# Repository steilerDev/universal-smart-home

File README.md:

# universal-smart-home

ESPHome firmware for the house: ~25 room sensor units plus a handful of special-purpose
nodes. Every device is an [Olimex ESP32-POE2](https://www.olimex.com/Products/IoT/ESP32/ESP32-POE2/open-source-hardware)
on PoE Ethernet — no WiFi, no cloud dependency. All devices integrate with Home
Assistant via the native ESPHome API. This repo is the single source of truth for
every device configuration.

---

## Hardware — Room Sensor

> [Schematic](https://app.cirkitdesigner.com/project/281a6c22-06b7-4593-8d16-d8be4f0f2b7c)

| Component | Part |
|-----------|------|
| MCU | [Olimex ESP32-POE2](https://www.olimex.com/Products/IoT/ESP32/ESP32-POE2/open-source-hardware) (ESP32-WROVER-E, PoE Ethernet) |
| Climate | [ENS160](https://esphome.io/components/sensor/ens160/) + [AHT21](https://esphome.io/components/sensor/aht10/) — eCO2, TVOC, AQI, temp, humidity |
| Illuminance | [BH1750](https://esphome.io/components/sensor/bh1750/) |
| Presence | [DFRobot C4002](https://www.dfrobot.com/product-3081.html) mmWave radar (custom component) |
| Dimmer | [KRIDA I2C AC dimmer](https://www.tindie.com/products/bugrovs2012/i2c-mosfet-trailing-edge-ac-dimmer-light) trailing-edge MOSFET (custom component) |
| GPIO Expander | [PCF8574](https://esphome.io/components/pcf8574/) — 2 buttons, 2 power circuits, 2 roller blinds |
| Status LED | WS2811/WS2812 via [esp32_rmt_led_strip](https://esphome.io/components/light/esp32_rmt_led_strip/) |
| Audio | [ES8311](https://esphome.io/components/audio_dac/es8311/) + NS4150B (notifications / TTS) |
| Power | [PZEM-004T](https://esphome.io/components/sensor/pzemac/) AC energy monitor |

PCB design files live in `hardware/pcb/`, the enclosure in `hardware/case/room-sensor/`.

---

## Hardware — Utility Sensor

The basement metering node. Same Olimex board, **no custom PCB** — the field wiring
lands on screw terminals — but it does have its own case (`hardware/case/utility-sensor/`).

| Component | Part |
|-----------|------|
| MCU | Olimex ESP32-POE2, running the `esp-idf` framework (8 × PCNT pulse counters) |
| Water flow | 8 × YF-B series hall-effect meters, one per supply line |
| Well level | QDY30A submersible level transmitter (Modbus RTU over RS485) |
| Grid power | Eastron SDM three-phase meter (Modbus RTU) — wired for, **not yet populated** |

Schematic (WIP): https://app.cirkitdesigner.com/project/46fdfdfb-f6f8-4aec-ac91-cfc2bc7dc07d

### Metered lines

| Line | GPIO | Line | GPIO |
|------|------|------|------|
| EG Kalt | GPIO04 | EG Warm | GPIO36 |
| OG Kalt | GPIO33 | OG Warm | GPIO13 |
| EG Heizung | GPIO15 | OG Heizung | GPIO02 |
| Anbau Heizung | GPIO14 | Brunnen | GPIO05 |

### Calibration

Both are build-time values in `devices/utility-sensor.yaml` — change and re-flash.

- **Water meters** — `flow_pulses_per_liter` per line. Meter datasheets quote
  `F = K * Q` (F in Hz, Q in L/min), so pulses/L is `K * 60`; the YF-B's K = 6.6 gives
  396. Each line carries its own value, so lines with a different meter model just get
  a different number.

  After changing a line's calibration, **re-flash and then press its
  `Water Volume Reset - <line>` button in HA**. The running total is stored in flash
  keyed by entity, so it survives the OTA and would otherwise keep the volume that
  was accumulated with the old pulses/L.
- **Well level** — the probe measures the water column above *itself*. The published
  value is the column above the **pump intake**:
  `raw + (well_pump_depth_cm - well_sensor_depth_cm)`. The offset is +100 cm in this
  install (probe at 15 m, intake at 16 m); it would be negative if the probe hung
  below the intake. Negative readings mean the water is below the intake and are not
  clamped away.

  ⚠️ Because the probe sits **above** the intake it cannot see a surface below itself,
  so the last 100 cm above the intake all read 100 cm — a floor, not a level. The
  `Well Probe Uncovered` binary sensor (`device_class: problem`) is ON exactly then, so
  automations can treat that reading as "≤100 cm, unknown" rather than trusting it.
  Hanging the probe below the intake would remove the blind spot.

### Home Assistant water dashboard

The `Water Volume - <line>` sensors carry `device_class: water` +
`state_class: total_increasing`, which is what HA's water dashboard filters on. A unit
of `L` alone is not enough — the entity simply never appears in the picker without
both of those.

---

## Repository Layout

```
devices/          — One YAML per physical device (substitutions + package includes)
packages/
  base/           — Board, Ethernet, OTA, HA API (room-sensor / utility-sensor variants)
  sensors/        — climate, illuminance, motion, power-pzem004t, water-flow,
                    well-level, energy-sdm
  actuators/      — status-led, dimmer, audio
  io/             — gpio-extender (PCF8574 — buttons, power circuits, blinds)
  displays/       — trmnl (e-ink dashboard)
components/       — Local custom ESPHome components (dfrobot_c4002, krida_dimmer, trmnl)
hardware/
  pcb/            — KiCad projects, symbol/footprint libs, LCSC BOM
  case/           — Fusion 360 enclosures, one directory per device
deploy/           — Device Builder deployment notes
scripts/          — validate-all, builder-deploy, deploy, new-device, check-device
sounds/           — WAV assets for the audio package
secrets.template.yaml
```

---

## Deployed Devices

| Device | IP | Packages |
|--------|----|---------|
| `room-sensor-poe2` (prototype) | 10.10.14.20 | base, power, climate, motion, status\_led |
| `eink-dashboard` | 10.10.14.25 | base, trmnl |
| `utility-sensor` | 10.10.14.10 | base, well\_level, 8 × water\_flow |

---

## Quick Start

Firmware is compiled and OTA-flashed by the self-hosted **ESPHome Device Builder**,
not by compiling locally — see [`deploy/README.md`](deploy/README.md).

```bash
cp secrets.template.yaml secrets.yaml  # fill in OTA password + HA encryption key

esphome config devices/<name>.yaml     # 1. validate (cheap, no compile)
./scripts/builder-deploy.py <name>     # 2. compile + OTA on the builder
./scripts/check-device.py <name>       # 3. post-deploy health check
```

Add a new device:

```bash
./scripts/new-device.sh <room-name>
```

Local compilation (`pip3 install esphome --break-system-packages`, then
`esphome run devices/<name>.yaml`) still works as a fallback; see `CLAUDE.md` for the
PlatformIO workarounds it needs.

---

## Packages

Each device YAML picks only the packages it needs. Every device requires exactly one
`base` package; the rest are optional.

| Package | Provides |
|---------|----------|
| `base/room-sensor` | Board (arduino), Ethernet PoE, OTA, HA API, I2C bus |
| `base/utility-sensor` | Board (esp-idf), Ethernet PoE, OTA, HA API — no I2C |
| `sensors/climate` | [ENS160](https://esphome.io/components/sensor/ens160/) + [AHT20](https://esphome.io/components/sensor/aht10/) — air quality, temp, humidity |
| `sensors/illuminance` | [BH1750](https://esphome.io/components/sensor/bh1750/) light level |
| `sensors/motion` | [DFRobot C4002](https://www.dfrobot.com/product-3081.html) presence + target tracking |
| `sensors/power-pzem004t` | [PZEM-004T](https://esphome.io/components/sensor/pzemac/) AC voltage/current/power/energy |
| `sensors/water-flow` | Pulse water meter for one supply line — include once per line with `vars` |
| `sensors/well-level` | QDY30A submersible level transmitter over Modbus |
| `sensors/energy-sdm` | Eastron SDM three-phase grid meter over Modbus |
| `actuators/dimmer` | [KRIDA I2C AC dimmer](https://www.tindie.com/products/bugrovs2012/i2c-mosfet-trailing-edge-ac-dimmer-light) (light entity) |
| `actuators/status-led` | WS2811/WS2812 status LED via [esp32_rmt_led_strip](https://esphome.io/components/light/esp32_rmt_led_strip/) |
| `actuators/audio` | [ES8311](https://esphome.io/components/audio_dac/es8311/) I2S media player |
| `io/gpio-extender` | [PCF8574](https://esphome.io/components/pcf8574/) — buttons, switches, blind covers |
| `displays/trmnl` | TRMNL BYOS e-ink dashboard client (custom component) |

`sensors/water-flow` is the one package meant to be included several times per device.
Use the mapping form of `!include` to pass it per-instance variables:

```yaml
packages:
  flow_eg_kalt: !include
    file: ../packages/sensors/water-flow.yaml
    vars:
      flow_key: eg_kalt
      flow_name: "EG Kalt"
      flow_pin: "GPIO04"
      flow_pulses_per_liter: "396"
```

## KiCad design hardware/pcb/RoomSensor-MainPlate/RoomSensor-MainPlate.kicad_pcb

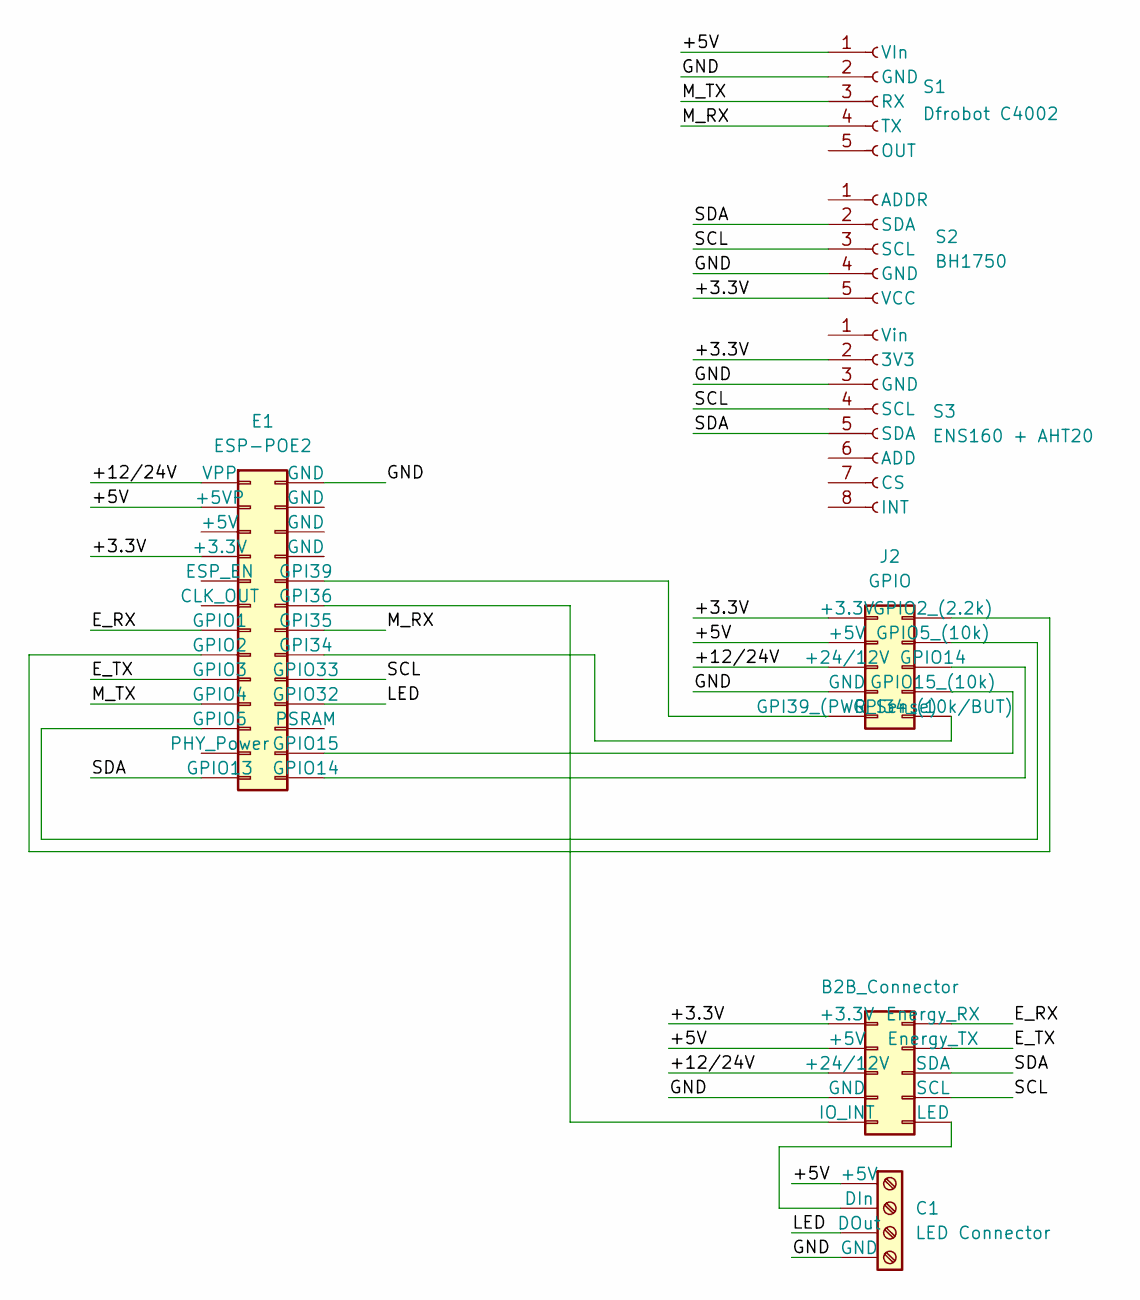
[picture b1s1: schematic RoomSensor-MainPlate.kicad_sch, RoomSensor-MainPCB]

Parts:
C1: LED Connector; TerminalBlock_Phoenix_MPT-0,5-4-2.54_1x04_P2.54mm_Horizontal; MPN KF128-2.54-4P
E1: ESP-POE2; PinSocket_2x13_P2.54mm_Vertical; MPN C64320
J1: B2B_Connector; B2B Connector; MPN MTB10-10S
J2: GPIO; IDC-Header_2x05_P2.54mm_Vertical; MPN MTB10-10S
S1: Dfrobot C4002; DFRobot C4002 Connector; MPN C50950
S2: BH1750; MPN C50950
S3: ENS160 + AHT20; ENS160 + AHT20 Connector; MPN C27438

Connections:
/+3.3V: E1.7 (+3.3V), J1.1 (+3.3V), J2.1 (+3.3V), S2.5 (VCC), S3.2 (3V3)
/+5V: C1.1 (+5V), E1.3 (+5VP), J1.3 (+5V), J2.3 (+5V), S1.1 (VIn)
/+12/24V: E1.1 (VPP), J1.5 (+24/12V), J2.5 (+24/12V)
/E_RX: E1.13 (GPIO1), J1.2 (Energy_RX)
/E_TX: E1.17 (GPIO3), J1.4 (Energy_TX)
/GND: C1.4 (GND), E1.2 (GND), J1.7 (GND), J2.7 (GND), S1.2 (GND), S2.4 (GND), S3.3 (GND)
/LED: C1.3 (DOut), E1.20 (GPIO32)
/M_RX: E1.14 (GPI35), S1.4 (TX)
/M_TX: E1.19 (GPIO4), S1.3 (RX)
/SCL: E1.18 (GPIO33), J1.8 (SCL), S2.3 (SCL), S3.4 (SCL)
/SDA: E1.25 (GPIO13), J1.6 (SDA), S2.2 (SDA), S3.5 (SDA)
unnamed: C1.2 (DIn), J1.10 (LED)
unnamed: E1.16 (GPI34), J2.10 (GPI34_(10k/BUT))
unnamed: E1.12 (GPI36), J1.9 (IO_INT)
unnamed: E1.10 (GPI39), J2.9 (GPI39_(PWR_Sense))
unnamed: E1.15 (GPIO2), J2.2 (GPIO2_(2.2k))
unnamed: E1.21 (GPIO5), J2.4 (GPIO5_(10k))
unnamed: E1.26 (GPIO14), J2.6 (GPIO14)
unnamed: E1.24 (GPIO15), J2.8 (GPIO15_(10k))

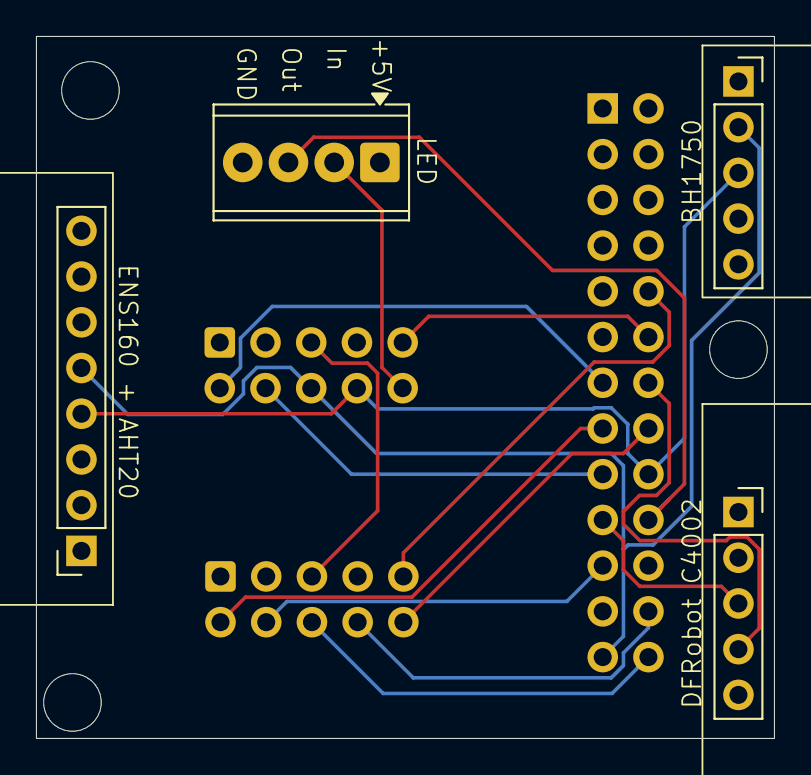
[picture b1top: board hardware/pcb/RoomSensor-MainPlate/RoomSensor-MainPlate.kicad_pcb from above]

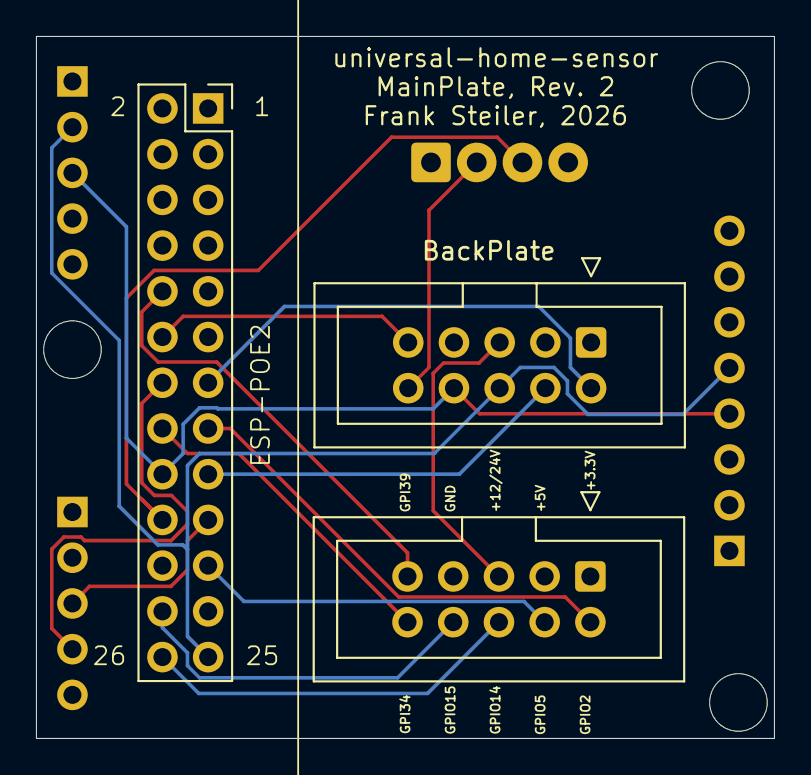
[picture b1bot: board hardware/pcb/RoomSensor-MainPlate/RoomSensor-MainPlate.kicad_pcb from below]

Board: 4 copper layers, 41.0 x 39.0 mm, 7 parts (3 on the bottom side), 19 nets.

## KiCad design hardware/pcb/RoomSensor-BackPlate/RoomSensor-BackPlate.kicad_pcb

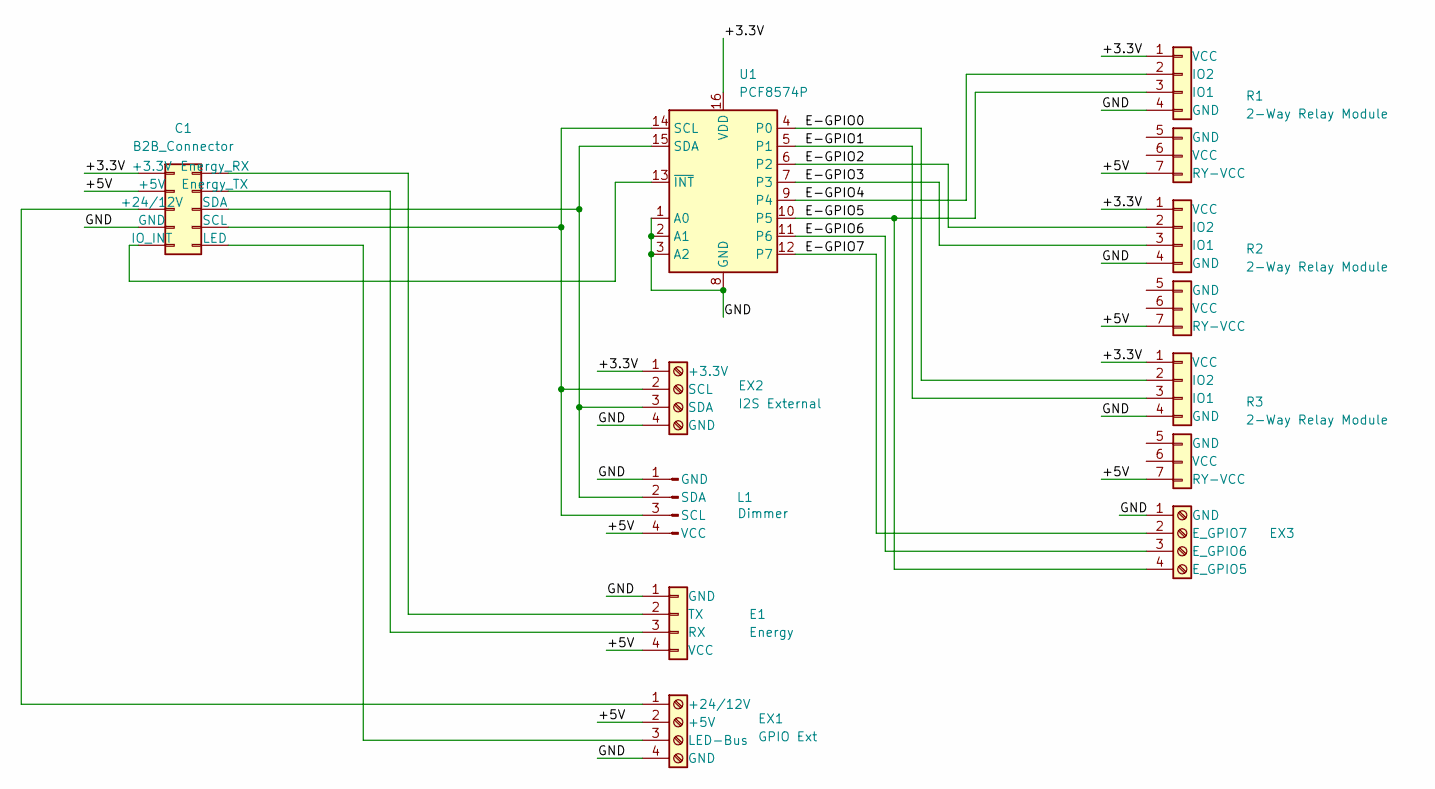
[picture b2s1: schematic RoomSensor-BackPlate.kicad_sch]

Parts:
C1: B2B_Connector; IDC-Header_2x05_P2.54mm_Vertical; MPN MTB10-10S
E1: Energy; PZEM-004T Connector; MPN HX PM2.54-1x4P ZC H11
EX1: GPIO Ext; TerminalBlock_Phoenix_MPT-0,5-4-2.54_1x04_P2.54mm_Horizontal; MPN KF128-2.54-4P
EX2: I2S External; TerminalBlock_Phoenix_MPT-0,5-4-2.54_1x04_P2.54mm_Horizontal; MPN KF128-2.54-4P
EX3: Buttons; TerminalBlock_Phoenix_MPT-0,5-4-2.54_1x04_P2.54mm_Horizontal; MPN KF128-2.54-4P
L1: Dimmer; Krida Dimmer I2C Connector; MPN HX PM2.54-1x4P ZC H11
R1, R2, R3: 2-Way Relay Module; 2-way Relay Connector; MPN HX PM2.54-1x4P ZC H11
U1: PCF8574P; DIP-16_W7.62mm; MPN PCF8574P

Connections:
/+3.3V: C1.1 (+3.3V), EX2.1 (+3.3V), R1.1 (VCC), R2.1 (VCC), R3.1 (VCC), U1.16 (VDD)
/+5V: C1.3 (+5V), E1.4 (VCC), EX1.2 (+5V), L1.4 (VCC), R1.7 (RY-VCC), R2.7 (RY-VCC), R3.7 (RY-VCC)
/E-GPIO0: R3.2 (IO2), U1.4 (P0)
/E-GPIO1: R3.3 (IO1), U1.5 (P1)
/E-GPIO2: R2.2 (IO2), U1.6 (P2)
/E-GPIO3: R2.3 (IO1), U1.7 (P3)
/E-GPIO4: R1.2 (IO2), U1.9 (P4)
/E-GPIO5: EX3.4 (E_GPIO5), R1.3 (IO1), U1.10 (P5)
/E-GPIO6: EX3.3 (E_GPIO6), U1.11 (P6)
/E-GPIO7: EX3.2 (E_GPIO7), U1.12 (P7)
/GND: C1.7 (GND), E1.1 (GND), EX1.4 (GND), EX2.4 (GND), EX3.1 (GND), L1.1 (GND), R1.4 (GND), R2.4 (GND), R3.4 (GND), U1.1 (A0), U1.2 (A1), U1.3 (A2), U1.8 (GND)
unnamed: C1.5 (+24/12V), EX1.1 (+24/12V)
unnamed: C1.2 (Energy_RX), E1.2 (TX)
unnamed: C1.4 (Energy_TX), E1.3 (RX)
unnamed: C1.9 (IO_INT), U1.13 (~INT)
unnamed: C1.10 (LED), EX1.3 (LED-Bus)
unnamed: C1.8 (SCL), EX2.2 (SCL), L1.3 (SCL), U1.14 (SCL)
unnamed: C1.6 (SDA), EX2.3 (SDA), L1.2 (SDA), U1.15 (SDA)

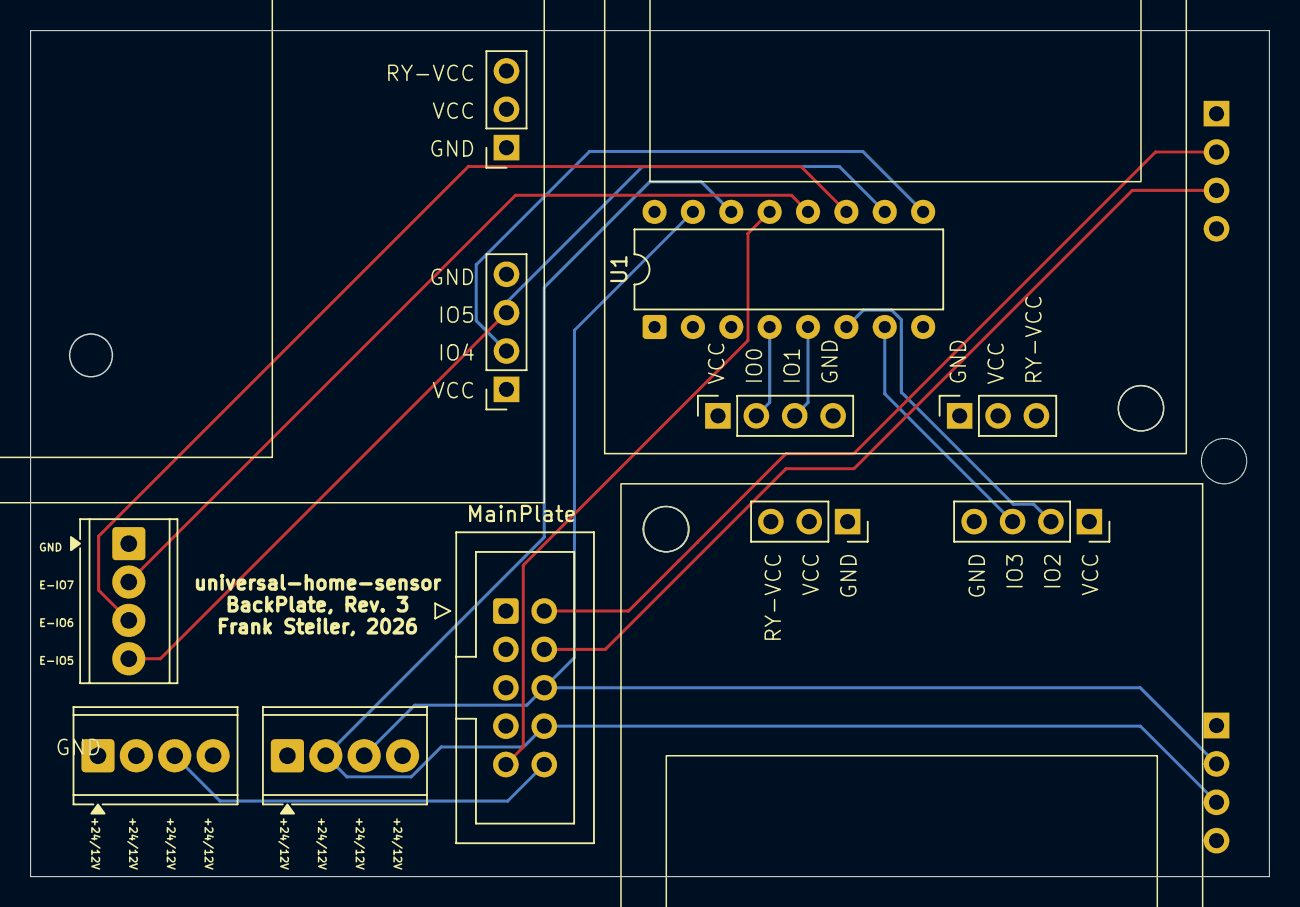
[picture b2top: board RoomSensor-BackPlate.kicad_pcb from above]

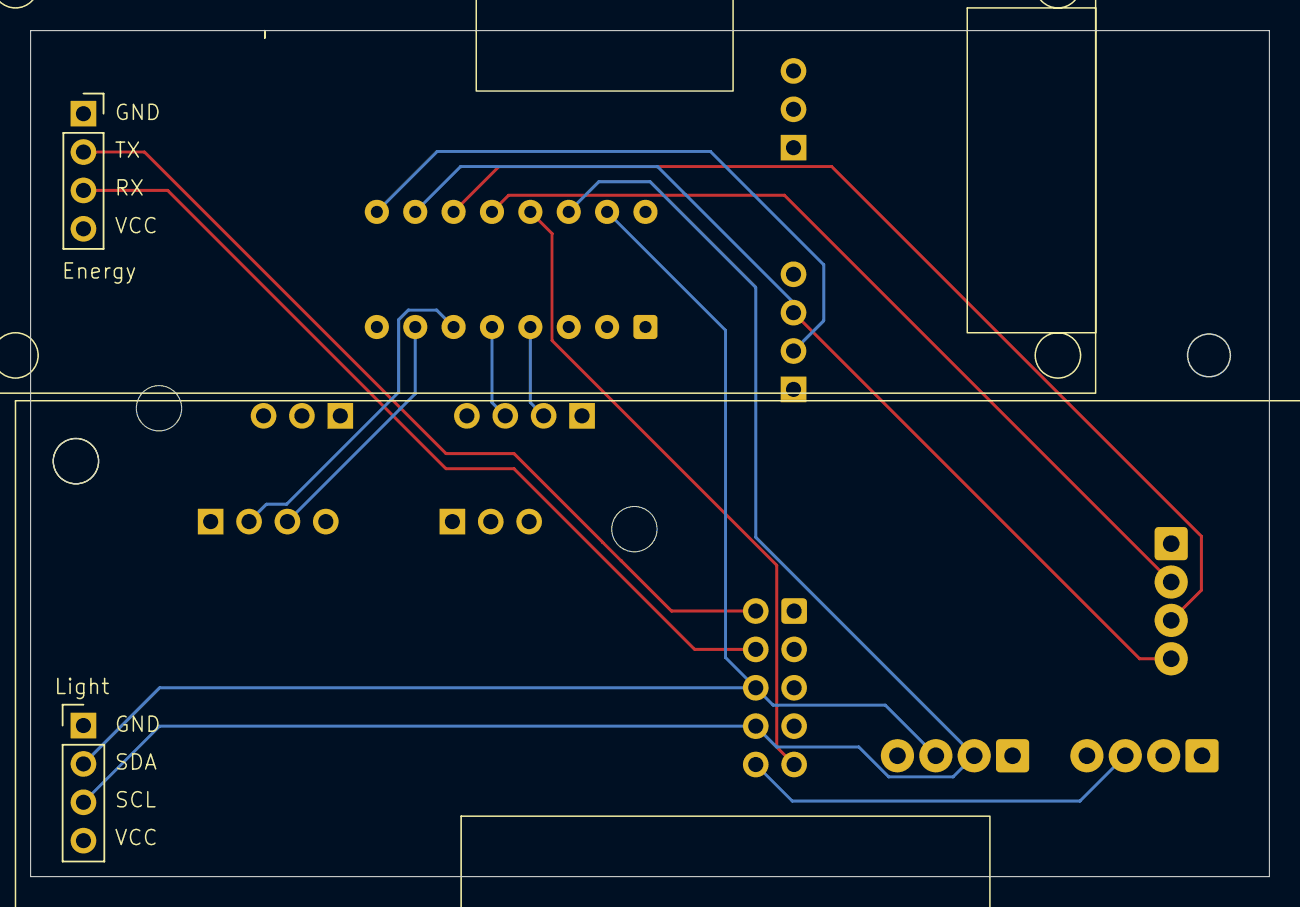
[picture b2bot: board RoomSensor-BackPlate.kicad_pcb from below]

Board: 4 copper layers, 82.0 x 56.0 mm, 10 parts (2 on the bottom side), 18 nets.

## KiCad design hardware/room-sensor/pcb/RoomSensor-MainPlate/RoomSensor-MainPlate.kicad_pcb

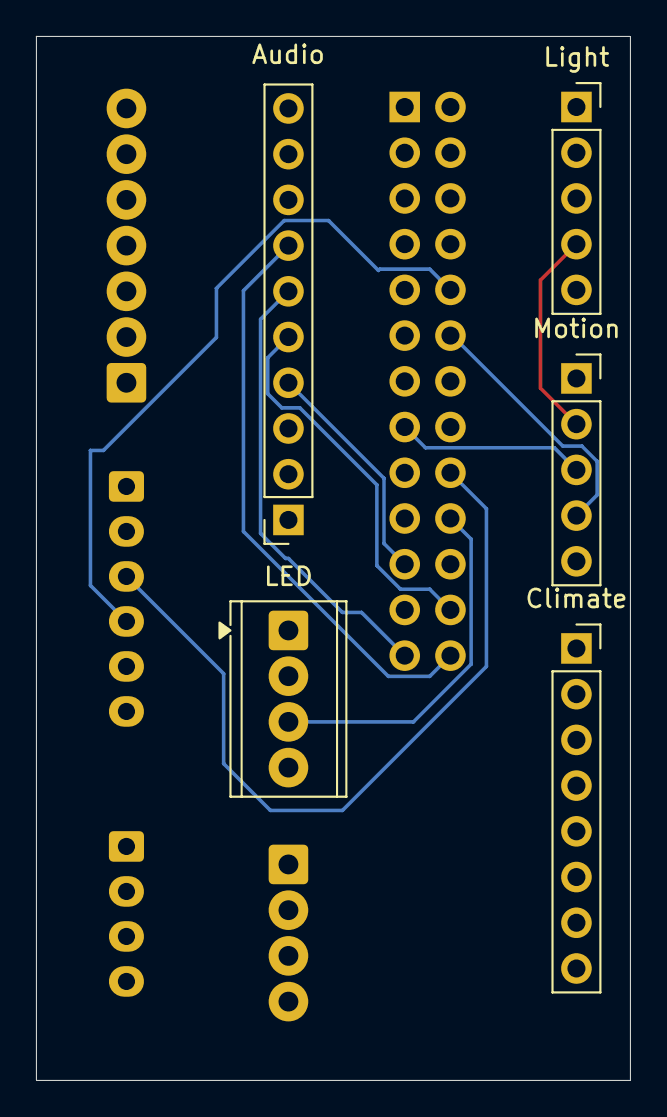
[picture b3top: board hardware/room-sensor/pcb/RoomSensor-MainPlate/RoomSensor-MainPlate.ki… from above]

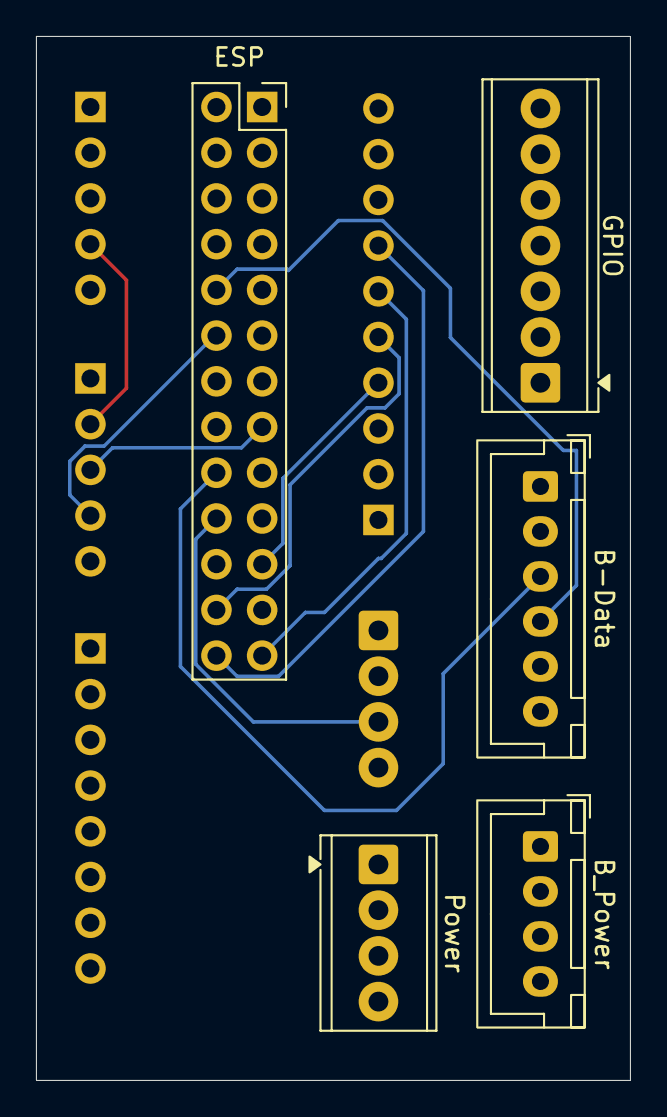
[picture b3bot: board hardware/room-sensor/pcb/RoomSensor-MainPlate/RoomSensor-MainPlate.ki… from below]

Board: 4 copper layers, 33.0 x 58.0 mm, 10 parts (5 on the bottom side), 19 nets.

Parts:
Audio: ES8311 + NS4150B; PinSocket_1x10_P2.54mm_Vertical
B-Data: Backplate Data; JST_XH_B6B-XH-A_1x06_P2.50mm_Vertical
B_Power: Backplate Power; JST_XH_B4B-XH-A_1x04_P2.50mm_Vertical
Climate: ENS160 + AHT20; PinSocket_1x08_P2.54mm_Vertical
ESP: ESP-POE2; PinSocket_2x13_P2.54mm_Vertical
GPIO: GPIO; TerminalBlock_Phoenix_MPT-0,5-7-2.54_1x07_P2.54mm_Horizontal
LED: LED Connector; TerminalBlock_Phoenix_MPT-0,5-4-2.54_1x04_P2.54mm_Horizontal
Light: BH1750; PinSocket_1x05_P2.54mm_Vertical
Motion: Dfrobot C4002; PinSocket_1x05_P2.54mm_Vertical
Power: Power; TerminalBlock_Phoenix_MPT-0,5-4-2.54_1x04_P2.54mm_Horizontal

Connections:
/+3.3V: Audio.8 (3V3), B_Power.1 (+3.3V), ESP.7 (+3.3V), Power.1 (+3.3V)
/+5V: Audio.9 (VCC), B_Power.2 (+5V), Climate.1 (Vin), ESP.3 (+5VP), LED.1 (+5V), Light.5 (VCC), Motion.1 (VIn), Power.2 (+5V)
/+12/24V: B_Power.3 (+24/12V), ESP.1 (VPP), Power.3 (+24/12V)
/A_BCLK: Audio.4 (BCK), ESP.21 (GPIO5), GPIO.2 (GPIO5)
/A_DI: Audio.5 (DI), B-Data.6 (GPIO15), ESP.24 (GPIO15), GPIO.3 (GPIO15)
/A_DO: Audio.7 (DO), ESP.26 (GPIO14), GPIO.5 (GPIO14)
/A_LRCLK: Audio.6 (WS), ESP.25 (GPIO13), GPIO.4 (GPIO13)
/A_MCLK: Audio.3 (MCK), ESP.13 (GPIO1), GPIO.1 (GPIO1)
/E_RX: B-Data.4 (Energy_RX), ESP.10 (GPI39)
/E_TX: B-Data.3 (Energy_TX), ESP.18 (GPIO33)
/GND: Audio.10 (GND), B_Power.4 (GND), Climate.3 (GND), ESP.2 (GND), LED.4 (GND), Light.4 (GND), Motion.2 (GND), Power.4 (GND)
/LED: ESP.20 (GPIO32), LED.3 (DIn)
/M_RX: ESP.12 (GPI36), Motion.4 (TX)
/M_TX: ESP.15 (GPIO2), Motion.3 (RX)
/SCL: Audio.2 (SCL), B-Data.2 (SCL), Climate.4 (SCL), ESP.17 (GPIO3), Light.3 (SCL)
/SDA: Audio.1 (SDA), B-Data.1 (SDA), Climate.5 (SDA), ESP.19 (GPIO4), Light.2 (SDA)
unnamed: B-Data.5 (LED_Bus), LED.2 (DOut)
unnamed: ESP.16 (GPI34), GPIO.6 (GPI34)
unnamed: ESP.14 (GPI35), GPIO.7 (GPI35)

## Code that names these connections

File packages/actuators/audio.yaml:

# Package: ES8311 + NS4150B — I2S Audio (notification sounds / TTS)
#
# ⚠️ Rev 1 boards only. The MainPlate Rev 2/3 dropped the ES8311/NS4150B section
# entirely, and two of the Rev 1 audio pins are now spoken for: GPIO13 is I2C SDA
# and GPIO1 is the PZEM UART RX. There are therefore no Rev 2/3 defaults here —
# every pin below stays a required substitution so that including this package on
# a Rev 2/3 device fails loudly instead of quietly fighting the I2C bus.
# Bus: I2C for DAC control (bus_i2c defined in base/room-sensor.yaml), I2S for audio data
# ES8311 address: 0x18
# Required substitutions:
#   audio_bclk_pin    — I2S bit clock       (e.g. "GPIO5")
#   audio_lrclk_pin   — I2S LR clock        (e.g. "GPIO13")
#   audio_dout_pin    — I2S data out to DAC  (e.g. "GPIO14")
#   audio_din_pin     — I2S data in from mic (e.g. "GPIO15")
#   audio_mclk_pin    — I2S MCLK output     (must be GPIO0/1/3 on ESP32 — hardware CLK_OUT pins only)
#   device_friendly_name
# Note: MCLK on GPIO1 requires UART0 logger disabled; add logger: baud_rate: 0 in the device file.

i2s_audio:
  - id: bus_i2s
    i2s_lrclk_pin: ${audio_lrclk_pin}
    i2s_bclk_pin: ${audio_bclk_pin}
    i2s_mclk_pin: ${audio_mclk_pin}

audio_dac:
  - platform: es8311
    id: es8311_dac
    address: 0x18
    use_mclk: true
    use_microphone: false

speaker:
  - platform: i2s_audio
    id: i2s_speaker
    i2s_audio_id: bus_i2s
    dac_type: external
    audio_dac: es8311_dac
    i2s_dout_pin: ${audio_dout_pin}

media_player:
  - platform: speaker
    name: "${device_friendly_name} Speaker"
    id: media_player_speaker
    buffer_size: 32768
    announcement_pipeline:
      speaker: i2s_speaker
      format: FLAC

rtttl:
  id: rtttl_beeper
  speaker: i2s_speaker

microphone:
  - platform: i2s_audio
    id: mic_i2s
    i2s_audio_id: bus_i2s
    i2s_din_pin: ${audio_din_pin}
    adc_type: external
    pdm: false

# --- Voice assistant (future) ---
# voice_assistant:
#   microphone: mic_i2s
#   media_player: media_player_speaker

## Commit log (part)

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2026-06-23 Initial PCB design
2026-06-24 PCB Design
